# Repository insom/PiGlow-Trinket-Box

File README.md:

PiGlow-Trinket-Box
==================

The build for this is [documented on my website][d].

STLs can be printed directly. 123dx files require Autodesk 123D to open.
Arduino code is working in IDE 1.6 and requires the TinyWireM library.
Flashing code to a Trinket requires the Adafruit board definitions. KiCad 4
can open the schematics, but the final Gerber files are also included in the
repository.

[d]: https://insom.github.io/project/piglow-adaptor/

License
-------

Copyright (c) 2016, Aaron Brady

Permission is hereby granted, free of charge, to any person obtaining a copy
of this software and associated documentation files (the "Software"), to deal
in the Software without restriction, including without limitation the rights
to use, copy, modify, merge, publish, distribute, sublicense, and/or sell
copies of the Software, and to permit persons to whom the Software is
furnished to do so, subject to the following conditions:

The above copyright notice and this permission notice shall be included in
all copies or substantial portions of the Software.

THE SOFTWARE IS PROVIDED "AS IS", WITHOUT WARRANTY OF ANY KIND, EXPRESS OR
IMPLIED, INCLUDING BUT NOT LIMITED TO THE WARRANTIES OF MERCHANTABILITY,
FITNESS FOR A PARTICULAR PURPOSE AND NONINFRINGEMENT. IN NO EVENT SHALL THE
AUTHORS OR COPYRIGHT HOLDERS BE LIABLE FOR ANY CLAIM, DAMAGES OR OTHER
LIABILITY, WHETHER IN AN ACTION OF CONTRACT, TORT OR OTHERWISE, ARISING FROM,
OUT OF OR IN CONNECTION WITH THE SOFTWARE OR THE USE OR OTHER DEALINGS IN
THE SOFTWARE.

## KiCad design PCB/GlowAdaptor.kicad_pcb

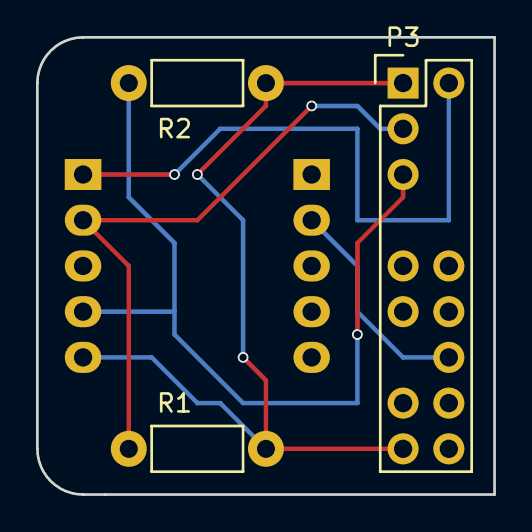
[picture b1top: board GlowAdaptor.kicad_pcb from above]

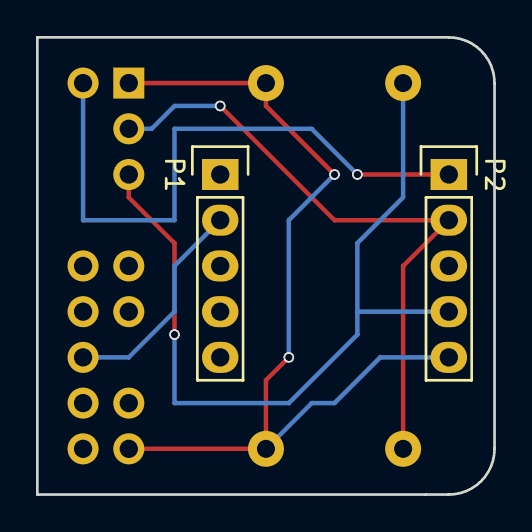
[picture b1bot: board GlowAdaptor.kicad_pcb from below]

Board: 2 copper layers, 25.4 x 25.4 mm, 5 parts (2 on the bottom side), 5 nets.

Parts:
P1: LEFT; Socket_Strip_Straight_1x05
P2: RIGHT; Socket_Strip_Straight_1x05
P3: PIGLOW; Pin_Header_Straight_2x09
R1, R2: R_Small; Resistor_Horizontal_RM7mm

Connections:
+3V3: P2.5, P3.1, P3.17, R1.1, R2.1
+5V: P2.1, P3.2
GND: P1.2, P3.14
unnamed: P2.2, P3.3, R1.2
unnamed: P2.4, P3.5, R2.2

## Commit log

2016-04-11 3D Things
2016-04-11 Arduino Code
2016-04-11 PCB Files
2016-04-11 REAMDE
